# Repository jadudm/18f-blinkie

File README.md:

Congratulations! Your 18F blinkie is artistnal, Maine-made craft electronics **that you can program to blink**. 

To make the blinkenlights go:

1. Plug the small end of the USB-C cable into the blinkie.
2. Plug the big end of the USB-C cable into a power source.

## Learn More for Great Awesome!

You can check out the [docs](https://jadud.com/18f-blinkie/) for more information about the 18F blinkie, including how to program new patterns.

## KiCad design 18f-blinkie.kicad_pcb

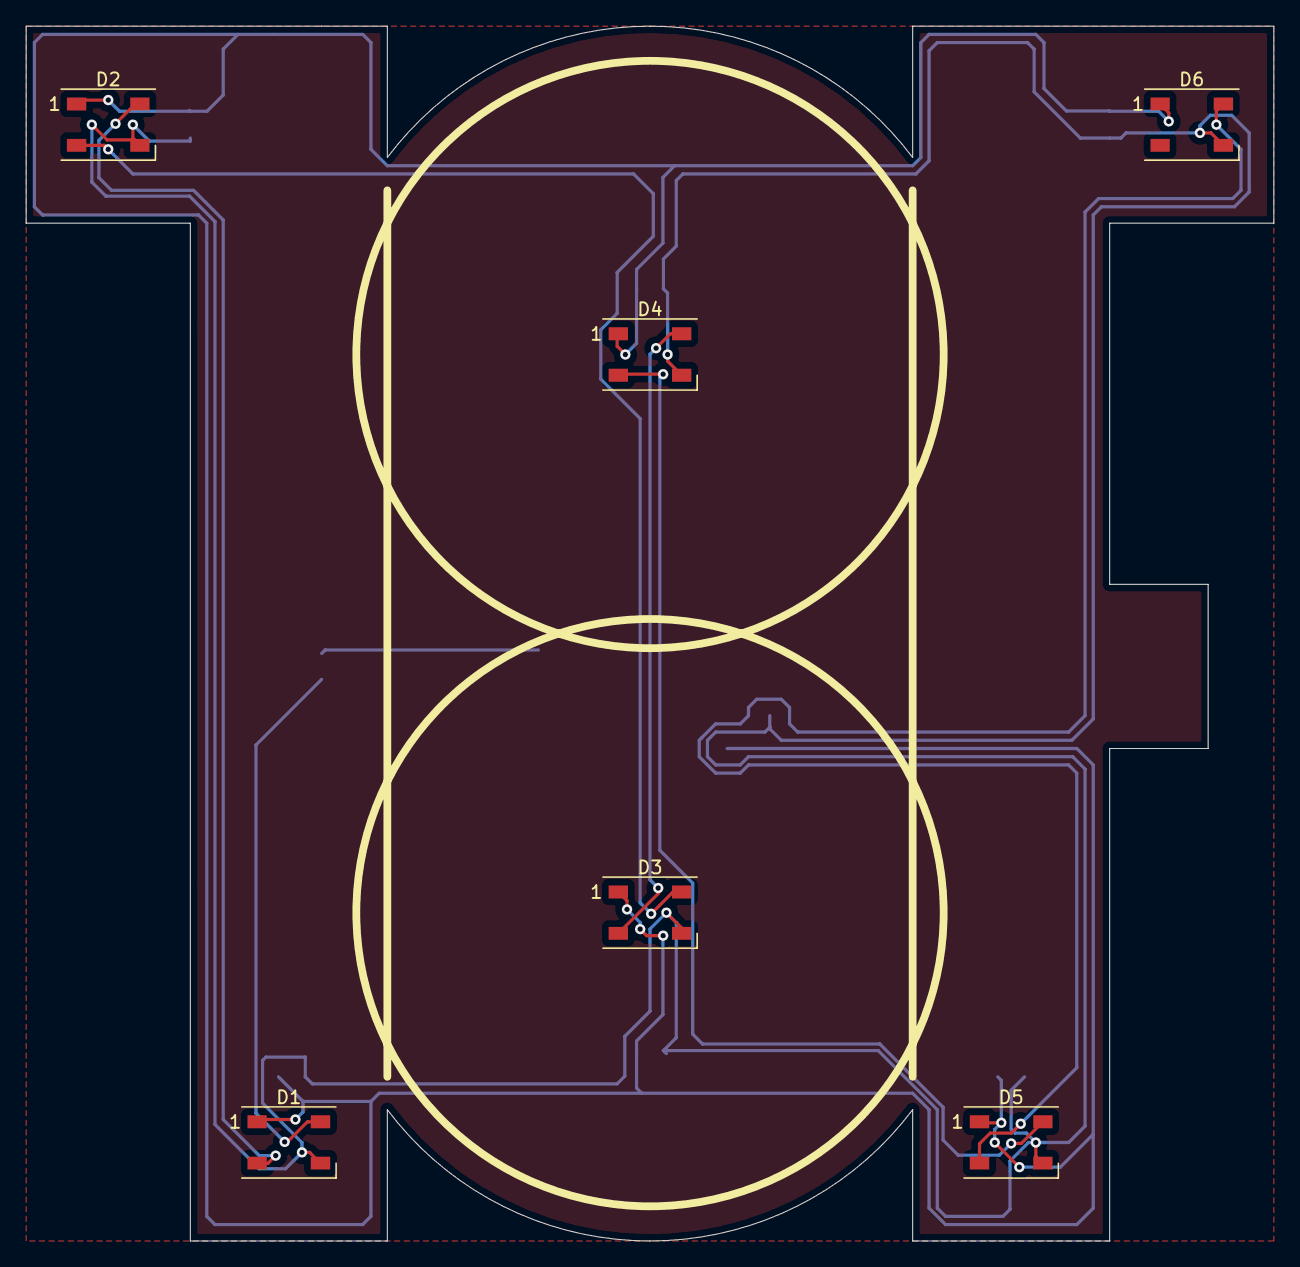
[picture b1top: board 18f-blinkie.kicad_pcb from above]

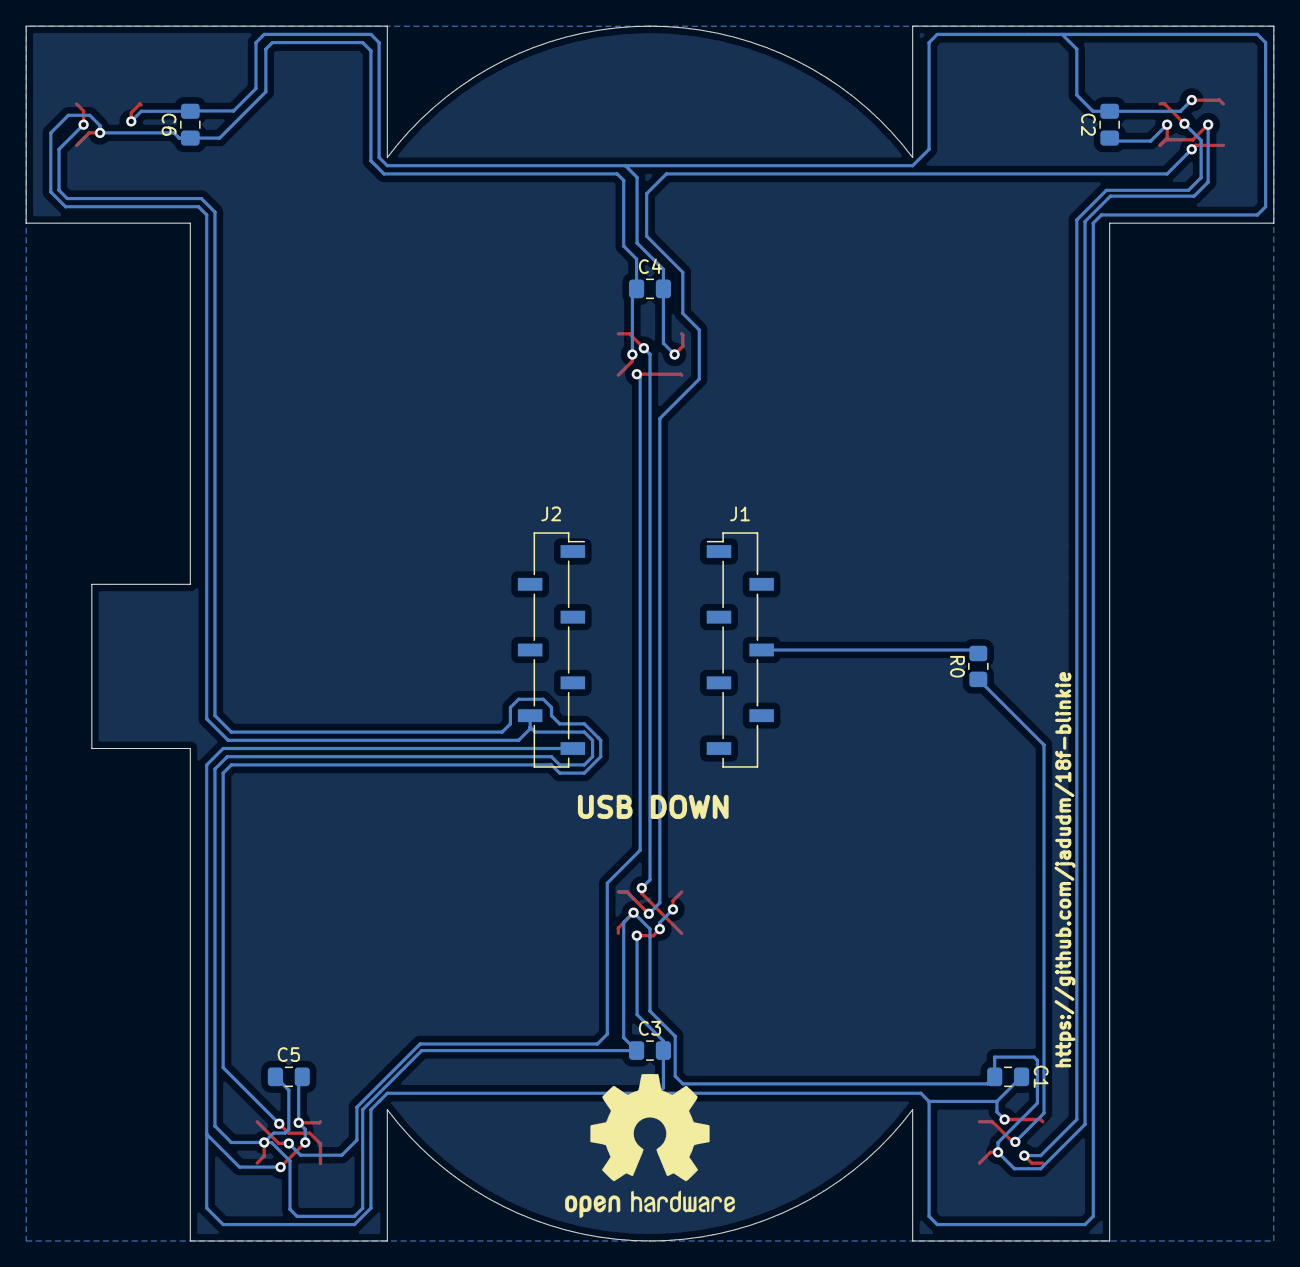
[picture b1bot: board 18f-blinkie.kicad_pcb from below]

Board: 2 copper layers, 96.5 x 94.0 mm, 15 parts (9 on the bottom side), 9 nets.

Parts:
C1, C2, C3, C4, C5, C6: C; C_0805_2012Metric_Pad1.18x1.45mm_HandSolder
D1, D2, D3, D4, D5, D6: WS2812B; LED_WS2812B_PLCC4_5.0x5.0mm_P3.2mm
J1: Conn_01x07_Female; PinSocket_1x07_P2.54mm_Vertical_SMD_Pin1Left
J2: Conn_01x07_Female; PinSocket_1x07_P2.54mm_Vertical_SMD_Pin1Right
R0: 220; R_0805_2012Metric_Pad1.20x1.40mm_HandSolder

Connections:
5V: C1.2, C2.2, C3.2, C4.2, C5.2, C6.2, D1.1, D2.1, D3.1, D4.1, D5.1, D6.1, J2.7
DATA: D1.4, R0.1
GND: C1.1, C2.1, C3.1, C4.1, C5.1, C6.1, D1.3, D2.3, D3.3, D4.3, D5.3, D6.3, J2.6
unnamed: D1.2, D2.4
unnamed: D2.2, D3.4
unnamed: D3.2, D4.4
unnamed: D4.2, D5.4
unnamed: D5.2, D6.4
unnamed: J1.4, R0.2

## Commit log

2020-11-10 Adding fill. Fixing text.
2020-11-10 Adding gerbers.
2020-12-05 Resized and retraced.
    The board was smaller than it had to be; why/how I did that, I do not know.
    Now, the board is close to the max dimension for low-cost fab. Wiring is
    neater, because I knew what I was doing. So, power/ground route around
    the edges (largely), and then I routed data.
    It is still the case that all vias are drilled *under* the LEDs, which
    maintains the appearance of the board.
2020-12-07 About to remove resistors.
2020-12-08 Removed resistors, submitted.
2020-12-19 Testing embeds.:
2020-12-19 Renaming.
2020-12-20 Reorganizing repos.
2020-12-20 Moving README back.
2020-12-23 Adding in docs.
    First pass at one-page docs.
2021-01-03 Ready for merge into main.
2021-01-03 Typo fix.
